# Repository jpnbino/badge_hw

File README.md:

# Badge - HW #

Design done based on the PIC12F1840

## PCB ##

## KiCad ##

The KiCad project is in `kicad/`. Open `kicad/BADGE.kicad_pro` to use the
native-imported schematic hierarchy and PCB. Project-local symbols are in
`kicad/BADGE.kicad_sym`, and imported footprints are in
`kicad/BADGE-import-fps.pretty/`; the corresponding library tables are kept
alongside the project so it is self-contained.

Generated fabrication and review artifacts are under `kicad/outputs/`.

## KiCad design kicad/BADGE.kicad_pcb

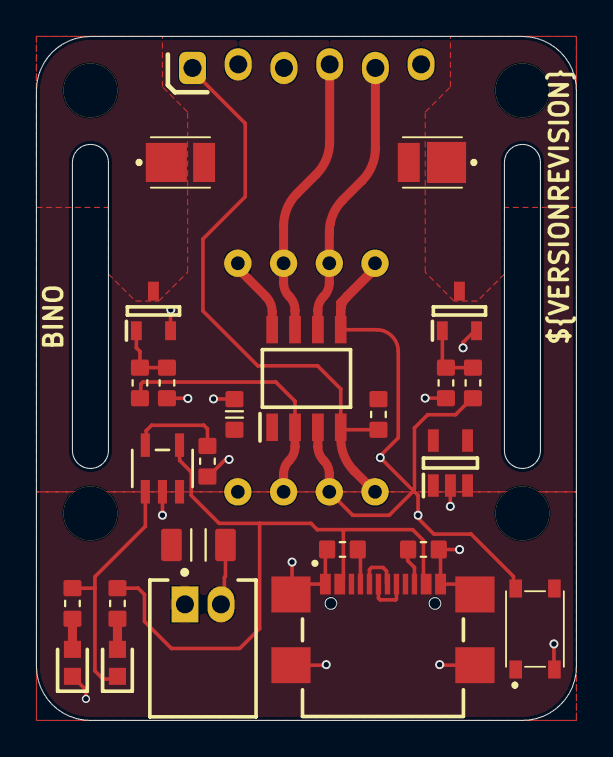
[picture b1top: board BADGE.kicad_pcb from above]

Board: 2 copper layers, 30.0 x 38.0 mm, 25 parts (0 on the bottom side), 22 nets.

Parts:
C1: approved sub OK; CAPC1608X90N
C2: approved sub OK; CAPC3216X180N
J1: USB4110-GF-A; GCT_USB4110-GF-A
J2: pickit3; CONN_ICSP
J3: S2B-PH-K-S(LF)(SN); JST-S2B-PH-K-S_V
LED1: 150060GS75000; LEDC1608X80N
LED2: 150060RS75000; LEDC1608X80N
LED3: S1W0-2835408003-0000003S-00005; STW8A12DMINJ18CAALL
LED4: S1W0-2835408003-0000003S-00005; STW8A12DMinJ18CAAll
PS1: NCP114ASN330T1G; SOT95P275X110-5N
Q1, Q2: 2N7002NXBKR; SOT95P230X110-3N
R1, R2, R3, R6, R7, R8, R9, R10: Thick Film; RESC1608X55N
R4, R5: RES 5.1K OHM 5% 1/10W 0603; RESC1608X55N
S1: PTS815_SJM_250_SMTR_LFS; PTS815SJM250SMTRLFS
U1: PIC12F1840-I_SN; SOIC127P600X175-8N
U2: MCP73831T-2ACI/OT; SOT-23-5_MC_MCH

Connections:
CC1: J1.A5, R5.2
CC2: J1.B5, R4.2
DN: J1.A7, J1.B7
DP: J1.A6, J1.B6
GND: C1.1, C2.2, J1.A1/B12, J1.B1/A12, J1.S1, J1.S2, J1.S3, J1.S4, J2.3, J3.2, LED1.1, PS1.2, Q1.2, Q2.2, R3.2, R4.1, R5.1, R9.2, R10.2, S1.3, U1.8, U2.2
ICSPCLK: J2.5, U1.6
ICSPDAT: J2.4, U1.7
NetLED1_2: LED1.2, R1.2
NetLED2_2: LED2.2, R2.2
NetLED3_1: LED3.1, Q1.3
NetLED4_1: LED4.1, Q2.3
NetQ1_1: Q1.1, R6.2, R9.1
NetQ2_1: Q2.1, R8.2, R10.1
NetR3_1: R3.1, U2.5
PWM1: R6.1, U1.2
PWM2: R8.1, U1.3
RA2: S1.2, U1.5
STAT: LED2.1, R1.1, U2.1
VBAT: C2.1, J3.1, PS1.1, PS1.3, U2.3
VCC3V3: C1.2, J2.2, LED3.2, LED4.2, PS1.5, R7.1, U1.1
VCC5V0: J1.A4/B9, J1.B4/A9, R2.1, U2.4
~MCLR: J2.1, R7.2, U1.4

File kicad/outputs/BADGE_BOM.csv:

"Reference","Value","Footprint","QUANTITY","Manufacturer","Manufacturer Part Number"
"C1","100n","BADGE:CAPC1608X90N","1","",""
"C2","10µ","BADGE:CAPC3216X180N","1","",""
"J1","*","BADGE:GCT_USB4110-GF-A","1","",""
"J2","=device","BADGE:CONN_ICSP","1","",""
"J3","S2B-PH-K-S(LF)(SN)","BADGE:JST-S2B-PH-K-S_V","1","",""
"LED1","150060GS75000","BADGE:LEDC1608X80N","1","",""
"LED2","150060RS75000","BADGE:LEDC1608X80N","1","",""
"LED3","S1W0-2835408003-0000003S-00005","BADGE:STW8A12DMinJ18CAAll","1","",""
"LED4","S1W0-2835408003-0000003S-00005","BADGE:STW8A12DMinJ18CAAll","1","",""
"PS1","NCP114ASN330T1G","BADGE:SOT95P275X110-5N","1","",""
"Q1","2N7002NXBKR","BADGE:SOT95P230X110-3N","1","",""
"Q2","2N7002NXBKR","BADGE:SOT95P230X110-3N","1","",""
"R1","1K","BADGE:RESC1608X55N","1","",""
"R2","1K","BADGE:RESC1608X55N","1","",""
"R3","10K","BADGE:RESC1608X55N","1","",""
"R4","5.1K","BADGE:RESC1608X55N","1","",""
"R5","5.1K","BADGE:RESC1608X55N","1","",""
"R6","1K","BADGE:RESC1608X55N","1","",""
"R7","10K","BADGE:RESC1608X55N","1","",""
"R8","1K","BADGE:RESC1608X55N","1","",""
"R9","1M","BADGE:RESC1608X55N","1","",""
"R10","1M","BADGE:RESC1608X55N","1","",""
"S1","PTS815_SJM_250_SMTR_LFS","BADGE:PTS815SJM250SMTRLFS","1","",""
"U1","PIC12F1840-I_SN","BADGE:SOIC127P600X175-8N","1","",""
"U2","MCP73831T-2ACI/OT","BADGE:SOT-23-5_MC_MCH","1","",""

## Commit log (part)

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2020-10-29 Added some components
2020-11-01 Routing on the way
2020-11-13 Close to an end. Fix the: DRC Generate files BOM GERBER LIBRARY
2020-11-24 Sent to production.
2020-12-02 Fixed 3D rendering problem.
2020-12-02 Fixed text alignment
2025-08-20 Add pcb images
2025-08-20 renamed files.
2025-08-20 Add resistors connecting to the LED.(R11 and R12) Fix connection R2.
